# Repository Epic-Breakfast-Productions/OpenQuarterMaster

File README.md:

# Open QuarterMaster

**Inventory without a catch, and all the hooks**

<!-- https://shields.io -->

<!-- ALL-CONTRIBUTORS-BADGE:START - Do not remove or modify this section -->

<!-- ALL-CONTRIBUTORS-BADGE:END -->

<details>
<summary>🛠 CI Status 🛠</summary>

## [Core](./software/core)

| Service                                               | Status                                                                                                                            |
|-------------------------------------------------------|-----------------------------------------------------------------------------------------------------------------------------------|
| [Core API](./software/core/oqm-core-api)              |              |
| [Base Station](./software/core/oqm-core-base-station) |  |

## [Plugins](./software/plugins)

| Service                                                         | Status                                                                                                                                        |
|-----------------------------------------------------------------|-----------------------------------------------------------------------------------------------------------------------------------------------|
| [External Item Search](./software/plugins/external-item-search) |  |
| [Storagotchi](./software/plugins/storagotchi)                   |             |

</details>

Open Quartermaster is an open source inventory management system, designed to be simple to use yet powerful and extendable. The last inventory management system you will ever need!

We are very much in active development, so check back often! We are also accepting any and all assistance, so feel free to report issues or feature requests, as well as pull requests! Additionally, feel free to ask questions in
the [Discussions](https://github.com/Epic-Breakfast-Productions/OpenQuarterMaster/discussions) or just hang out with us on our [Discord](https://discord.gg/cpcVh6SyNn)

## Quick Links

All documentation can be found on https://docs.openquartermaster.com

- For a quick start running on your own computer, check out [Single Host Deployment](deployment/Single%20Host)
- To see all the ways you can deploy OQM for yourself, see [Deployment](deployment/)
- For information on the overall system, see the [software](software/) directory.

> [!TIP]
> Newcomer? Giving OQM a try? Got suggestions? Feedback? First time contributors (with accepted contibutions) get free stickers from our [shop](https://openquartermaster.com/public/shop)!

## How it works

How we accomplish the goal of being the only inventory management system you could ever need is through our modular design. The main component of Open QuarterMaster is the [Core API](software/core/oqm-core-api). Think of this as the central
hub and core functionality of the system. It handles all the generic inventory management tasks; what is stored where, and facts about what is stored. This central component is designed to be, on the whole, generic and accessible. We also
have a frontend for the core API called the [Base Station](software/core/oqm-core-base-station), which lets you have direct and easy to navigate access to your inventory.

To cover specific use-cases, we have what we call [Plugins](software/plugins). These are components that extend the functionality of the basic inventory management, and fill additional needs with their own capabilities. Examples could
include Smart Refrigerator integrations, a system for interacting with physical storage mediums, Point of Sale Systems, Workflow management.. the list is endless. You could even create your own!

In the theme of flexibility, the system is designed to be run in many different environments. It is just as home on the cloud as well as something as small as a [Raspberry Pi](https://www.raspberrypi.com/). This is accomplished using
containers, segmenting each software component, ensuring flexibility and ease of management.

To get started on your own hardware, please see [Single Host Deployment](deployment/Single%20Host)

For more information on the overall system, see the [software](software/) directory.

## On Privacy

Being an open initiative, we take great care to ensure you are in control of your own data. None of the software we include here phones home at all, with the brief exception of Station Captain, which looks to this Git repository for
installations and updates. If you have a simple setup on your own hardware, you can expect your data to stay with you, and not transmitted anywhere by the software we include here. The sole exception is when you voluntarily and very optionally [register your instance](https://openquartermaster.com/public/instance-registration)

## Contributors ✨

Thanks goes to these wonderful people ([emoji key](https://allcontributors.org/docs/en/emoji-key)):

<!-- ALL-CONTRIBUTORS-LIST:START - Do not remove or modify this section -->
<!-- prettier-ignore-start -->
<!-- markdownlint-disable -->
<table>
  <tbody>
    <tr>
      <td align="center" valign="top" width="14.28%"><a href="http://gjstewart.net"><br /><sub><b>Greg Stewart</b></sub></a><br /><a href="https://github.com/Epic-Breakfast-Productions/OpenQuarterMaster/issues?q=author%3AGregJohnStewart" title="Bug reports">🐛</a> <a href="#business-GregJohnStewart" title="Business development">💼</a> <a href="https://github.com/Epic-Breakfast-Productions/OpenQuarterMaster/commits?author=GregJohnStewart" title="Code">💻</a> <a href="#content-GregJohnStewart" title="Content">🖋</a> <a href="#data-GregJohnStewart" title="Data">🔣</a> <a href="https://github.com/Epic-Breakfast-Productions/OpenQuarterMaster/commits?author=GregJohnStewart" title="Documentation">📖</a> <a href="#design-GregJohnStewart" title="Design">🎨</a> <a href="#ideas-GregJohnStewart" title="Ideas, Planning, & Feedback">🤔</a> <a href="#infra-GregJohnStewart" title="Infrastructure (Hosting, Build-Tools, etc)">🚇</a> <a href="#maintenance-GregJohnStewart" title="Maintenance">🚧</a> <a href="#projectManagement-GregJohnStewart" title="Project Management">📆</a> <a href="#tool-GregJohnStewart" title="Tools">🔧</a> <a href="https://github.com/Epic-Breakfast-Productions/OpenQuarterMaster/commits?author=GregJohnStewart" title="Tests">⚠️</a></td>
      <td align="center" valign="top" width="14.28%"><a href="https://github.com/anixon-rh"><br /><sub><b>Anthony Nixon</b></sub></a><br /><a href="#infra-anixon-rh" title="Infrastructure (Hosting, Build-Tools, etc)">🚇</a> <a href="#mentoring-anixon-rh" title="Mentoring">🧑‍🏫</a></td>
      <td align="center" valign="top" width="14.28%"><a href="https://github.com/kfrankli"><br /><sub><b>kfrankli</b></sub></a><br /><a href="https://github.com/Epic-Breakfast-Productions/OpenQuarterMaster/commits?author=kfrankli" title="Documentation">📖</a></td>
      <td align="center" valign="top" width="14.28%"><a href="https://github.com/ajoline"><br /><sub><b>ajoline</b></sub></a><br /><a href="#mentoring-ajoline" title="Mentoring">🧑‍🏫</a> <a href="https://github.com/Epic-Breakfast-Productions/OpenQuarterMaster/pulls?q=is%3Apr+reviewed-by%3Aajoline" title="Reviewed Pull Requests">👀</a> <a href="#security-ajoline" title="Security">🛡️</a></td>
      <td align="center" valign="top" width="14.28%"><a href="https://github.com/piercde12"><br /><sub><b>piercde12</b></sub></a><br /><a href="#business-piercde12" title="Business development">💼</a> <a href="#content-piercde12" title="Content">🖋</a> <a href="https://github.com/Epic-Breakfast-Productions/OpenQuarterMaster/commits?author=piercde12" title="Documentation">📖</a> <a href="#design-piercde12" title="Design">🎨</a> <a href="https://github.com/Epic-Breakfast-Productions/OpenQuarterMaster/commits?author=piercde12" title="Tests">⚠️</a> <a href="#userTesting-piercde12" title="User Testing">📓</a></td>
      <td align="center" valign="top" width="14.28%"><a href="https://github.com/kyleclarktech"><br /><sub><b>Kyle Clark</b></sub></a><br /><a href="#content-kyleclarktech" title="Content">🖋</a> <a href="#ideas-kyleclarktech" title="Ideas, Planning, & Feedback">🤔</a> <a href="#mentoring-kyleclarktech" title="Mentoring">🧑‍🏫</a> <a href="https://github.com/Epic-Breakfast-Productions/OpenQuarterMaster/pulls?q=is%3Apr+reviewed-by%3Akyleclarktech" title="Reviewed Pull Requests">👀</a> <a href="#security-kyleclarktech" title="Security">🛡️</a> <a href="https://github.com/Epic-Breakfast-Productions/OpenQuarterMaster/commits?author=kyleclarktech" title="Tests">⚠️</a> <a href="#userTesting-kyleclarktech" title="User Testing">📓</a></td>
      <td align="center" valign="top" width="14.28%"><a href="https://github.com/DanielKrejska"><br /><sub><b>DanielKrejska</b></sub></a><br /><a href="https://github.com/Epic-Breakfast-Productions/OpenQuarterMaster/commits?author=DanielKrejska" title="Code">💻</a></td>
    </tr>
    <tr>
      <td align="center" valign="top" width="14.28%"><a href="https://github.com/LouisBarbier"><br /><sub><b>LouisBarbier</b></sub></a><br /><a href="#content-LouisBarbier" title="Content">🖋</a> <a href="#projectManagement-LouisBarbier" title="Project Management">📆</a></td>
      <td align="center" valign="top" width="14.28%"><a href="https://github.com/BrendanAndrews"><br /><sub><b>Brendan Andrews</b></sub></a><br /><a href="https://github.com/Epic-Breakfast-Productions/OpenQuarterMaster/commits?author=BrendanAndrews" title="Code">💻</a></td>
      <td align="center" valign="top" width="14.28%"><a href="https://github.com/Spitzer-Tech"><br /><sub><b>Spitzer-Tech</b></sub></a><br /><a href="https://github.com/Epic-Breakfast-Productions/OpenQuarterMaster/issues?q=author%3ASpitzer-Tech" title="Bug reports">🐛</a> <a href="#design-Spitzer-Tech" title="Design">🎨</a> <a href="#example-Spitzer-Tech" title="Examples">💡</a> <a href="#financial-Spitzer-Tech" title="Financial">💵</a> <a href="https://github.com/Epic-Breakfast-Productions/OpenQuarterMaster/commits?author=Spitzer-Tech" title="Tests">⚠️</a> <a href="#userTesting-Spitzer-Tech" title="User Testing">📓</a> <a href="#ideas-Spitzer-Tech" title="Ideas, Planning, & Feedback">🤔</a></td>
      <td align="center" valign="top" width="14.28%"><a href="https://github.com/steve-dill"><br /><sub><b>steve-dill</b></sub></a><br /><a href="https://github.com/Epic-Breakfast-Productions/OpenQuarterMaster/issues?q=author%3Asteve-dill" title="Bug reports">🐛</a> <a href="https://github.com/Epic-Breakfast-Productions/OpenQuarterMaster/commits?author=steve-dill" title="Code">💻</a> <a href="#ideas-steve-dill" title="Ideas, Planning, & Feedback">🤔</a> <a href="#infra-steve-dill" title="Infrastructure (Hosting, Build-Tools, etc)">🚇</a> <a href="#mentoring-steve-dill" title="Mentoring">🧑‍🏫</a> <a href="#tool-steve-dill" title="Tools">🔧</a> <a href="#userTesting-steve-dill" title="User Testing">📓</a> <a href="#maintenance-steve-dill" title="Maintenance">🚧</a> <a href="https://github.com/Epic-Breakfast-Productions/OpenQuarterMaster/pulls?q=is%3Apr+reviewed-by%3Asteve-dill" title="Reviewed Pull Requests">👀</a> <a href="https://github.com/Epic-Breakfast-Productions/OpenQuarterMaster/commits?author=steve-dill" title="Tests">⚠️</a></td>
      <td align="center" valign="top" width="14.28%"><a href="https://github.com/mulliar22"><br /><sub><b>mulliar22</b></sub></a><br /><a href="https://github.com/Epic-Breakfast-Productions/OpenQuarterMaster/commits?author=mulliar22" title="Code">💻</a> <a href="#data-mulliar22" title="Data">🔣</a> <a href="https://github.com/Epic-Breakfast-Productions/OpenQuarterMaster/commits?author=mulliar22" title="Documentation">📖</a> <a href="#example-mulliar22" title="Examples">💡</a> <a href="#plugin-mulliar22" title="Plugin/utility libraries">🔌</a> <a href="#research-mulliar22" title="Research">🔬</a></td>
      <td align="center" valign="top" width="14.28%"><a href="https://github.com/mallom21"><br /><sub><b>mallom21</b></sub></a><br /><a href="https://github.com/Epic-Breakfast-Productions/OpenQuarterMaster/commits?author=mallom21" title="Code">💻</a> <a href="#data-mallom21" title="Data">🔣</a> <a href="https://github.com/Epic-Breakfast-Productions/OpenQuarterMaster/commits?author=mallom21" title="Documentation">📖</a> <a href="#example-mallom21" title="Examples">💡</a> <a href="#plugin-mallom21" title="Plugin/utility libraries">🔌</a> <a href="#research-mallom21" title="Research">🔬</a> <a href="#projectManagement-mallom21" title="Project Management">📆</a></td>
      <td align="center" valign="top" width="14.28%"><a href="https://github.com/Coletrane315"><br /><sub><b>Coletrane315</b></sub></a><br /><a href="https://github.com/Epic-Breakfast-Productions/OpenQuarterMaster/commits?author=Coletrane315" title="Code">💻</a> <a href="#data-Coletrane315" title="Data">🔣</a> <a href="https://github.com/Epic-Breakfast-Productions/OpenQuarterMaster/commits?author=Coletrane315" title="Documentation">📖</a> <a href="#example-Coletrane315" title="Examples">💡</a> <a href="#plugin-Coletrane315" title="Plugin/utility libraries">🔌</a> <a href="#research-Coletrane315" title="Research">🔬</a></td>
    </tr>
    <tr>
      <td align="center" valign="top" width="14.28%"><a href="https://github.com/simonramsey0"><br /><sub><b>Simon Ramsey</b></sub></a><br /><a href="https://github.com/Epic-Breakfast-Productions/OpenQuarterMaster/commits?author=simonramsey0" title="Code">💻</a> <a href="#content-simonramsey0" title="Content">🖋</a> <a href="#plugin-simonramsey0" title="Plugin/utility libraries">🔌</a> <a href="#research-simonramsey0" title="Research">🔬</a></td>
      <td align="center" valign="top" width="14.28%"><a href="https://github.com/RaimonAbreu007"><br /><sub><b>RaimonAbreu007</b></sub></a><br /><a href="https://github.com/Epic-Breakfast-Productions/OpenQuarterMaster/commits?author=RaimonAbreu007" title="Code">💻</a> <a href="#content-RaimonAbreu007" title="Content">🖋</a> <a href="#plugin-RaimonAbreu007" title="Plugin/utility libraries">🔌</a> <a href="#research-RaimonAbreu007" title="Research">🔬</a> <a href="#projectManagement-RaimonAbreu007" title="Project Management">📆</a></td>
      <td align="center" valign="top" width="14.28%"><a href="https://github.com/Maxf653"><br /><sub><b>Max</b></sub></a><br /><a href="#content-Maxf653" title="Content">🖋</a> <a href="#plugin-Maxf653" title="Plugin/utility libraries">🔌</a> <a href="#research-Maxf653" title="Research">🔬</a></td>
      <td align="center" valign="top" width="14.28%"><a href="https://github.com/thederpylama"><br /><sub><b>Ian Lauver</b></sub></a><br /><a href="https://github.com/Epic-Breakfast-Productions/OpenQuarterMaster/commits?author=thederpylama" title="Code">💻</a> <a href="#content-thederpylama" title="Content">🖋</a> <a href="#plugin-thederpylama" title="Plugin/utility libraries">🔌</a> <a href="#research-thederpylama" title="Research">🔬</a></td>
      <td align="center" valign="top" width="14.28%"><a href="https://github.com/CircuitSide"><br /><sub><b>CircuitSide</b></sub></a><br /><a href="https://github.com/Epic-Breakfast-Productions/OpenQuarterMaster/issues?q=author%3ACircuitSide" title="Bug reports">🐛</a> <a href="#business-CircuitSide" title="Business development">💼</a> <a href="https://github.com/Epic-Breakfast-Productions/OpenQuarterMaster/commits?author=CircuitSide" title="Code">💻</a> <a href="#content-CircuitSide" title="Content">🖋</a> <a href="#data-CircuitSide" title="Data">🔣</a> <a href="https://github.com/Epic-Breakfast-Productions/OpenQuarterMaster/commits?author=CircuitSide" title="Documentation">📖</a> <a href="#design-CircuitSide" title="Design">🎨</a> <a href="#ideas-CircuitSide" title="Ideas, Planning, & Feedback">🤔</a> <a href="#promotion-CircuitSide" title="Promotion">📣</a> <a href="#research-CircuitSide" title="Research">🔬</a> <a href="https://github.com/Epic-Breakfast-Productions/OpenQuarterMaster/pulls?q=is%3Apr+reviewed-by%3ACircuitSide" title="Reviewed Pull Requests">👀</a> <a href="https://github.com/Epic-Breakfast-Productions/OpenQuarterMaster/commits?author=CircuitSide" title="Tests">⚠️</a> <a href="#userTesting-CircuitSide" title="User Testing">📓</a></td>
      <td align="center" valign="top" width="14.28%"><a href="http://cv.axgiri.tech"><br /><sub><b>Aidyn A.</b></sub></a><br /><a href="https://github.com/Epic-Breakfast-Productions/OpenQuarterMaster/commits?author=axgiri" title="Code">💻</a> <a href="#maintenance-axgiri" title="Maintenance">🚧</a> <a href="#plugin-axgiri" title="Plugin/utility libraries">🔌</a> <a href="https://github.com/Epic-Breakfast-Productions/OpenQuarterMaster/pulls?q=is%3Apr+reviewed-by%3Aaxgiri" title="Reviewed Pull Requests">👀</a> <a href="https://github.com/Epic-Breakfast-Productions/OpenQuarterMaster/commits?author=axgiri" title="Tests">⚠️</a> <a href="#research-axgiri" title="Research">🔬</a></td>
      <td align="center" valign="top" width="14.28%"><a href="https://github.com/SanchitPanchwatikar"><br /><sub><b>Sanchit Panchwatikar</b></sub></a><br /><a href="https://github.com/Epic-Breakfast-Productions/OpenQuarterMaster/commits?author=SanchitPanchwatikar" title="Code">💻</a></td>
    </tr>
    <tr>
      <td align="center" valign="top" width="14.28%"><a href="https://github.com/jasecolino"><br /><sub><b>Jase Colino</b></sub></a><br /><a href="https://github.com/Epic-Breakfast-Productions/OpenQuarterMaster/commits?author=jasecolino" title="Code">💻</a> <a href="#design-jasecolino" title="Design">🎨</a> <a href="#research-jasecolino" title="Research">🔬</a></td>
      <td align="center" valign="top" width="14.28%"><a href="https://github.com/kyleighpea123"><br /><sub><b>kyleighpea123</b></sub></a><br /><a href="https://github.com/Epic-Breakfast-Productions/OpenQuarterMaster/commits?author=kyleighpea123" title="Code">💻</a> <a href="#design-kyleighpea123" title="Design">🎨</a> <a href="#research-kyleighpea123" title="Research">🔬</a></td>
      <td align="center" valign="top" width="14.28%"><a href="https://github.com/elsamlt"><br /><sub><b>elsamlt</b></sub></a><br /><a href="https://github.com/Epic-Breakfast-Productions/OpenQuarterMaster/commits?author=elsamlt" title="Code">💻</a> <a href="#design-elsamlt" title="Design">🎨</a> <a href="#research-elsamlt" title="Research">🔬</a></td>
      <td align="center" valign="top" width="14.28%"><a href="https://github.com/JakeElston"><br /><sub><b>Jake Elston</b></sub></a><br /><a href="https://github.com/Epic-Breakfast-Productions/OpenQuarterMaster/commits?author=JakeElston" title="Code">💻</a> <a href="#design-JakeElston" title="Design">🎨</a> <a href="#research-JakeElston" title="Research">🔬</a></td>
      <td align="center" valign="top" width="14.28%"><a href="https://github.com/hongshengy"><br /><sub><b>hongshengy</b></sub></a><br /><a href="#security-hongshengy" title="Security">🛡️</a></td>
    </tr>
  </tbody>
</table>

<!-- markdownlint-restore -->
<!-- prettier-ignore-end -->

<!-- ALL-CONTRIBUTORS-LIST:END -->

This project follows the [all-contributors](https://github.com/all-contributors/all-contributors) specification. Contributions of any kind welcome!

## Star History

<a href="https://www.star-history.com/?repos=epic-breakfast-productions%2Fopenquartermaster&type=date&legend=bottom-right">
 <picture>
   <source media="(prefers-color-scheme: dark)" srcset="https://api.star-history.com/chart?repos=epic-breakfast-productions/openquartermaster&type=date&theme=dark&legend=bottom-right" />
   <source media="(prefers-color-scheme: light)" srcset="https://api.star-history.com/chart?repos=epic-breakfast-productions/openquartermaster&type=date&legend=bottom-right" />
   
 </picture>
</a>

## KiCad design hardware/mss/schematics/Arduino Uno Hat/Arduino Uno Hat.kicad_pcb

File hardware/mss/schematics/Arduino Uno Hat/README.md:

# OQM MSS Arduino Uno Hat

This is a Kicad project to create the PCB for the MSS Module controller hat for the Arduino Uno.

## Steps after updating

Steps after updating schematics/pcb:

 1. Write out BOM
    1. Schematic View
    1. Tools -> Generate Bill of Materials
    1. Select `outputs/OQM MSS Arduino Hat BOM.csv`
    1. Hit Export
 1. Update PCB
    1. PCB View
    1. Hit Update PCB from schematic (F8)
    1. Fill all zones (Edit -> Fill All Zones) (B)
 1. New Image
    1. PCB View
    1. 3D-Viewer (alt-3)
    1. Setup nice, squareish image
    1. Enable raytracing
    1. File -> export current fiew as JPEG, saving to outputs folder
   
## Get outputs for fabrication

 1. Put outputs in `outputs/fab/`
 1. For upload to PCBway, put all files in fab dir into a zip file.

References:

 - https://docs.kicad.org/8.0/en/getting_started_in_kicad/getting_started_in_kicad.html#fab

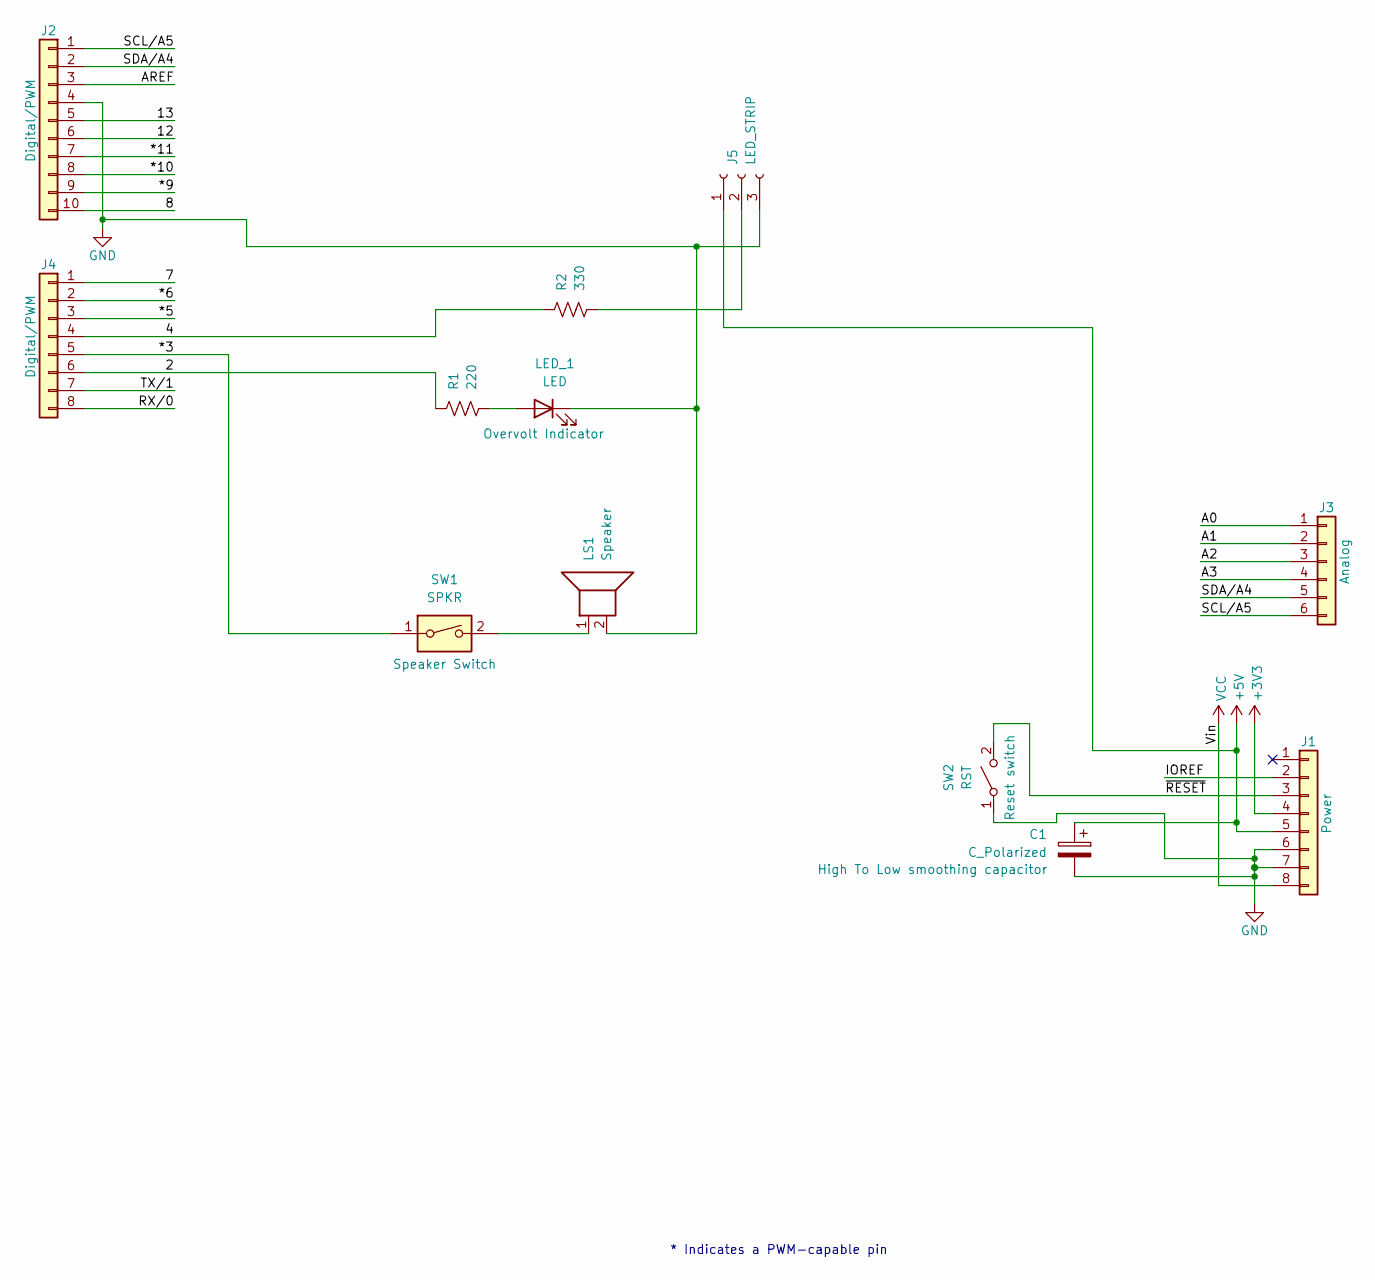
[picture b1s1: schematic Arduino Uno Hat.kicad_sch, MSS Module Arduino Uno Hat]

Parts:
C1: C_Polarized; CP_Radial_D4.0mm_P1.50mm
J1: Power; PinSocket_1x08_P2.54mm_Vertical
J2: Digital/PWM; PinSocket_1x10_P2.54mm_Vertical
J3: Analog; PinSocket_1x06_P2.54mm_Vertical
J4: Digital/PWM; PinSocket_1x08_P2.54mm_Vertical
J5: LED_STRIP; JST_XH_S3B-XH-A-1_1x03_P2.50mm_Horizontal
LED_1: LED; LED_D5.0mm
LS1: Speaker; Buzzer_15x7.5RM7.6
R1: 220; R_Axial_DIN0309_L9.0mm_D3.2mm_P12.70mm_Horizontal
R2: 330; R_Axial_DIN0309_L9.0mm_D3.2mm_P12.70mm_Horizontal
SW1: SPKR; SW_DIP_SPSTx01_Slide_6.7x4.1mm_W7.62mm_P2.54mm_LowProfile
SW2: RST; SW_PUSH_1P1T_6x3.5mm_H5.0_APEM_MJTP1250

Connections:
+3V3: J1.4
+5V: C1.1, J1.5, J5.1
/2: J4.6, R1.1
/4: J4.4, R2.1
/7: J4.1
/8: J2.10
/12: J2.6
/13: J2.5
/*3: J4.5, SW1.1
/*5: J4.3
/*6: J4.2
/*9: J2.9
/*10: J2.8
/*11: J2.7
/A0: J3.1
/A1: J3.2
/A2: J3.3
/A3: J3.4
/AREF: J2.3
/IOREF: J1.2
/RX/0: J4.8
/SCL/A5: J2.1, J3.6
/SDA/A4: J2.2, J3.5
/TX/1: J4.7
/~RESET: J1.3, SW2.2 (B)
GND: C1.2, J1.6, J1.7, J2.4, J5.3, LED_1.1 (K), LS1.2, SW2.1 (A)
unnamed: J5.2, R2.2
unnamed: LED_1.2 (A), R1.2
unnamed: LS1.1, SW1.2
VCC: J1.8

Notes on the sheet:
* Indicates a PWM-capable pin

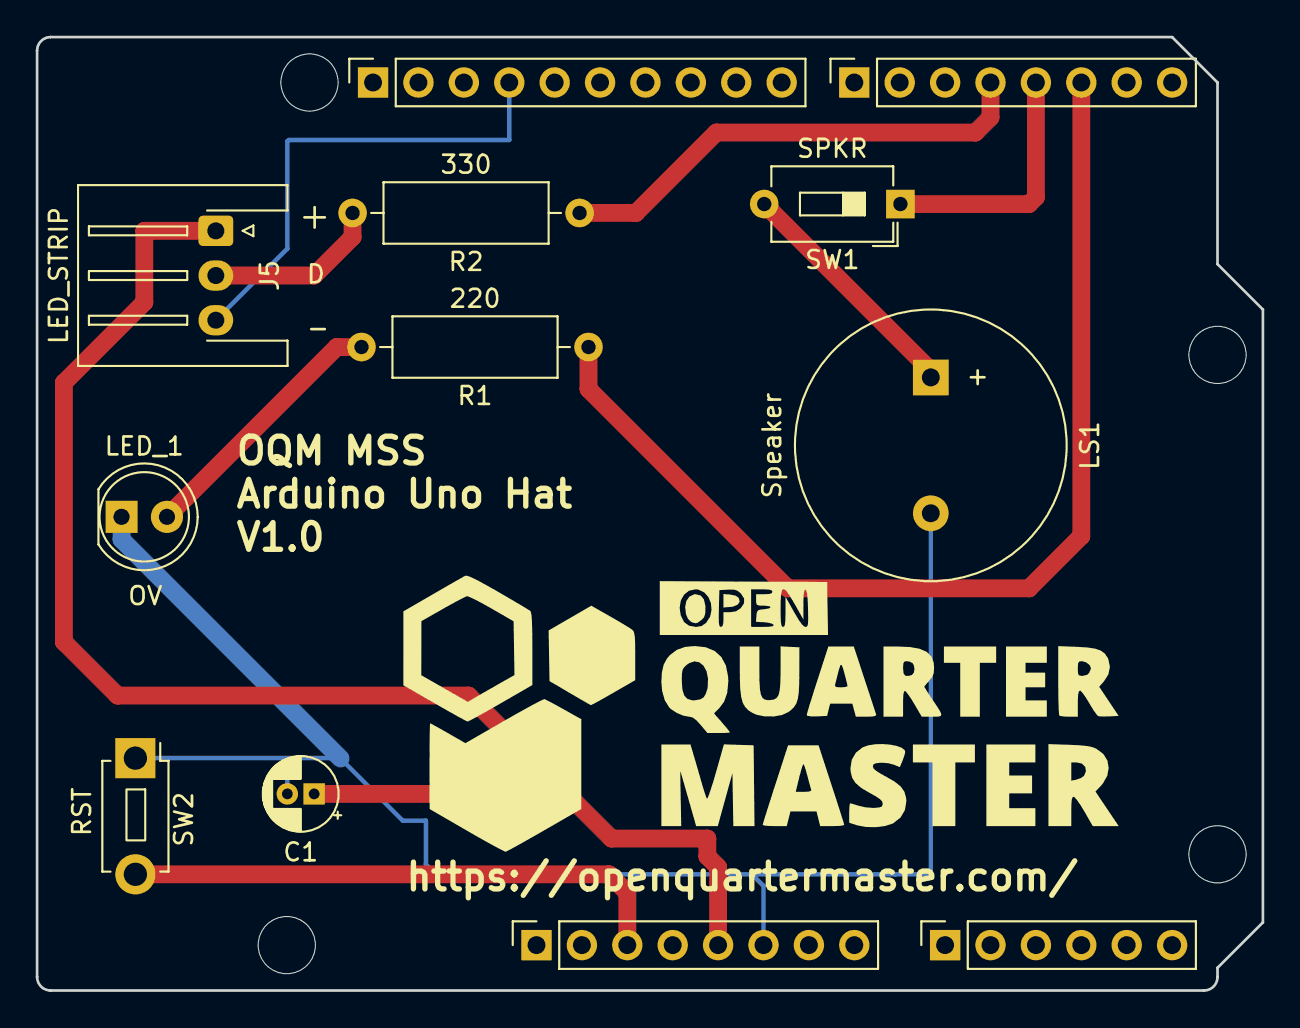
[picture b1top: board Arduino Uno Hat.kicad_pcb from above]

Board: 2 copper layers, 68.6 x 53.3 mm, 17 parts (0 on the bottom side), 11 nets.

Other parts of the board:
MH1, MH2, MH3, MH4: MountingHole_3.2mm
OQM_Logo: LOGO
